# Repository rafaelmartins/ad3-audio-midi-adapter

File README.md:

# ad3-audio-midi-adapter

Audio/MIDI Adapter for Analog Discovery 3

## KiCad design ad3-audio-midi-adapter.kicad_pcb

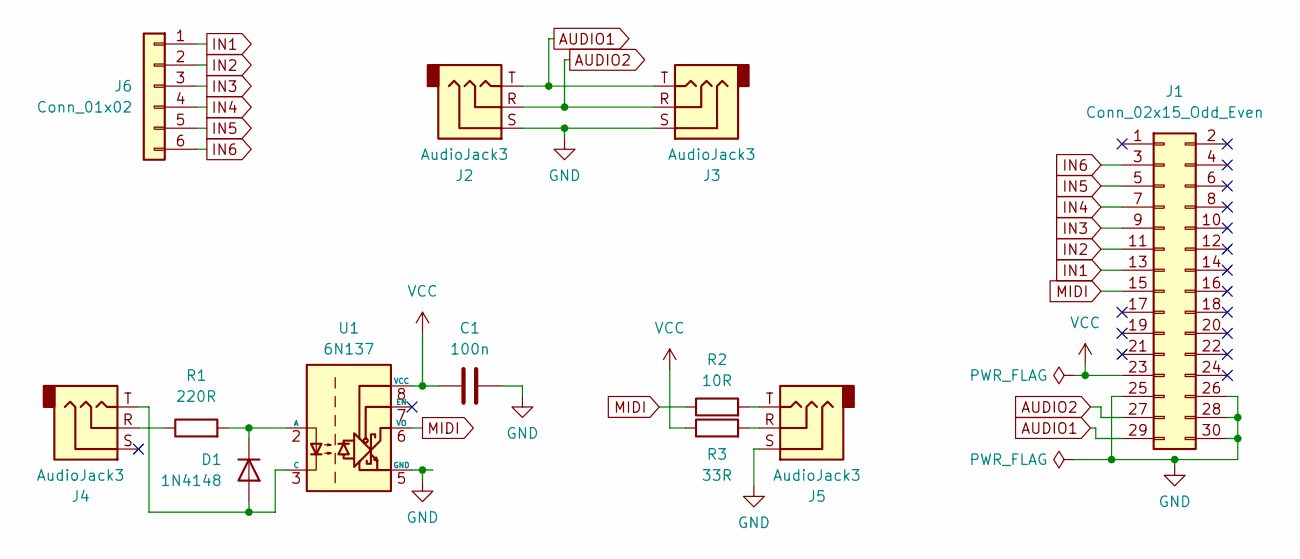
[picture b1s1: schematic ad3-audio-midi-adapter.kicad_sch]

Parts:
C1: 100n; C_Disc_D4.3mm_W1.9mm_P5.00mm
D1: 1N4148; D_DO-35_SOD27_P7.62mm_Horizontal
J1: Conn_02x15_Odd_Even; PinSocket_2x15_P2.54mm_Horizontal
J2, J3, J4, J5: AudioJack3; Jack_3.5mm_STX-3120-3B_Horizontal
J6: Conn_01x02; PinHeader_1x06_P2.54mm_Vertical
R1: 220R; R_Axial_DIN0207_L6.3mm_D2.5mm_P10.16mm_Horizontal
R2: 10R; R_Axial_DIN0207_L6.3mm_D2.5mm_P10.16mm_Horizontal
R3: 33R; R_Axial_DIN0207_L6.3mm_D2.5mm_P10.16mm_Horizontal
U1: 6N137; DIP-8_W7.62mm

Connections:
AUDIO1: J1.29, J2.T, J3.T
AUDIO2: J1.27, J2.R, J3.R
GND: C1.2, J1.25, J1.26, J1.28, J1.30, J2.S, J3.S, J5.S, U1.5 (GND)
IN1: J1.13, J6.1
IN2: J1.11, J6.2
IN3: J1.9, J6.3
IN4: J1.7, J6.4
IN5: J1.5, J6.5
IN6: J1.3, J6.6
MIDI: J1.15, R2.1, U1.6 (VO)
unnamed: D1.2 (A), J4.T, U1.3 (C)
unnamed: D1.1 (K), R1.2, U1.2 (A)
unnamed: J4.R, R1.1
unnamed: J5.R, R3.2
unnamed: J5.T, R2.2
VCC: C1.1, J1.23, R3.1, U1.8 (VCC)

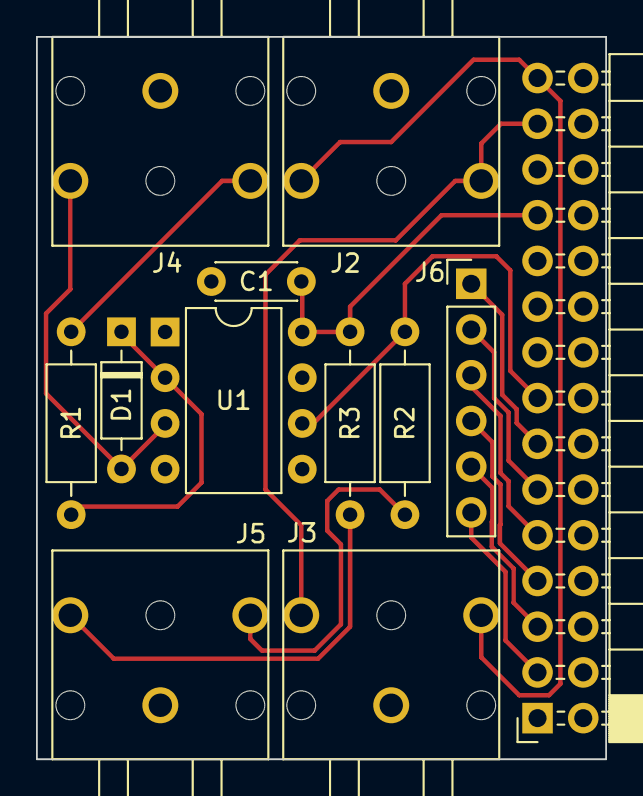
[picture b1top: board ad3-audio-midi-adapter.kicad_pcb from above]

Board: 2 copper layers, 31.6 x 40.1 mm, 12 parts (0 on the bottom side), 16 nets.

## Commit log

2023-09-19 add 3d renderings
